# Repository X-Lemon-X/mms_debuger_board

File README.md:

## Board  debug for ModualCard system Rj45 connector
### Input
- 12V xt30 connector
- USB-C connector for MMS<-PC communication USB 2.0 compatible
- CAN1 and CAN2 molex microfit 2x2 connectors.
- 2x can termination switches
- Reverse polarity protection
### Output
- Rj45 connector for ModualCard system

### RJ45 Pinout
| Pin | Function | Description |
|-----|----------|---------------------------------------------|
| 1   | CAN1 L   | CAN 1 Low speed up to 1 Mb/s                |
| 2   | CAN1 H   | CAN 1 High speed up to 1 Mb/s               |
| 3   | GND      | 500mA                                       |
| 4   | CAN2 L   | CAN 2 Low speed up to 5 Mb/s                |
| 5   | CAN2 H   | CAN 2 High speed up to 5 Mb/s               |
| 6   | 12V      | 500 mA                                      |
| 7   | USB D-   | USB data plus                               |
| 8   | USB D+   | USB data minus                              |

### Images

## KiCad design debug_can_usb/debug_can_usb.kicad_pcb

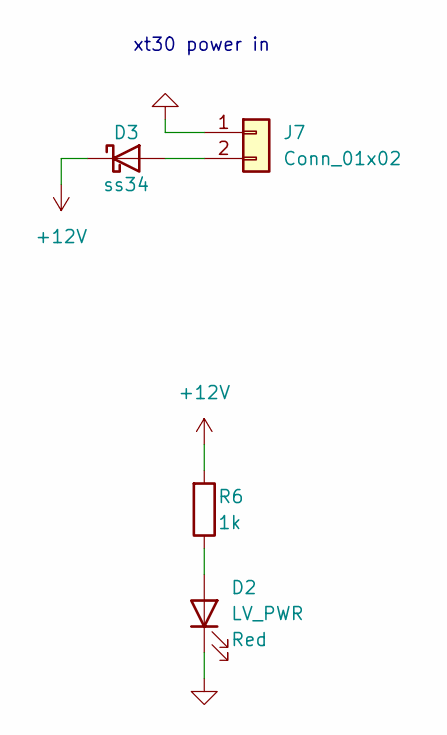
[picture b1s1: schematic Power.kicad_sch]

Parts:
D2: LV_PWR; D_0603_1608Metric
D3: ss34; D_SMA
J7: Conn_01x02; AMASS_XT30PW-M_1x02_P2.50mm_Horizontal
R6: 1k; R_0402_1005Metric

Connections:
+12V: D3.1 (K), R6.2; also elsewhere on the board
GND: D2.1 (K), J7.1; also elsewhere on the board
unnamed: D2.2 (A), R6.1
unnamed: D3.2 (A), J7.2

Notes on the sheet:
xt30 power in

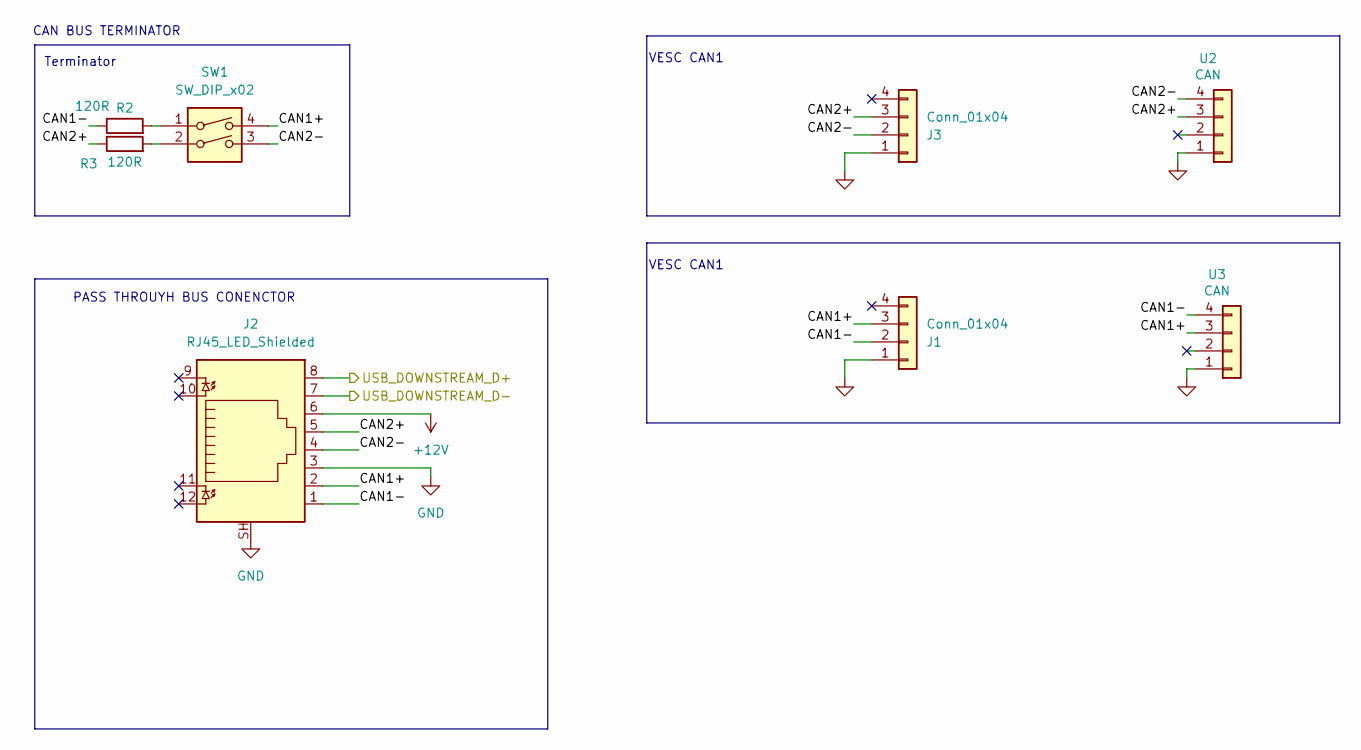
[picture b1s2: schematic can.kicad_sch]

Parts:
J1, J3: Conn_01x04; JST_XH_B4B-XH-A_1x04_P2.50mm_Vertical
J2: RJ45_LED_Shielded; RJ45_Amphenol_RJHSE538X
R2, R3: 120R; R_0603_1608Metric
SW1: SW_DIP_x02; SW_DIP_SPSTx02_Slide_6.7x6.64mm_W7.62mm_P2.54mm_LowProfile
U2, U3: CAN; Molex_Micro-Fit_3.0_43045-0412_2x02_P3.00mm_Vertical

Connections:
+12V: J2.6; also elsewhere on the board
/CAN/CAN1+: J1.3, J2.2, SW1.4, U3.3
/CAN/CAN1-: J1.2, J2.1, R2.1, U3.4
/CAN/CAN2+: J2.5, J3.3, R3.1, U2.3
/CAN/CAN2-: J2.4, J3.2, SW1.3, U2.4
/CAN/USB_DOWNSTREAM_D+: J2.8; also elsewhere on the board
/CAN/USB_DOWNSTREAM_D-: J2.7; also elsewhere on the board
GND: J1.1, J2.3, J2.SH, J3.1, U2.1, U3.1; also elsewhere on the board
unnamed: R2.2, SW1.1
unnamed: R3.2, SW1.2

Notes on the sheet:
PASS THROUYH BUS CONENCTOR
CAN BUS TERMINATOR
VESC CAN1
Terminator

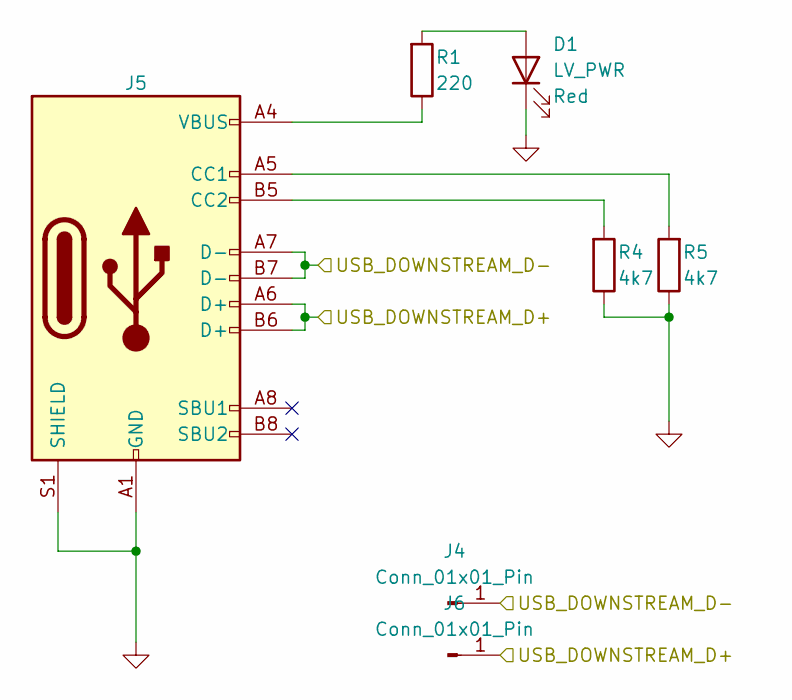
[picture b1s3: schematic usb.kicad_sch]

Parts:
D1: LV_PWR; D_0603_1608Metric
J4, J6: Conn_01x01_Pin; PinHeader_1x01_P2.54mm_Vertical
J5: USB_C_Receptacle_USB2.0; USB_C_Receptacle_G-Switch_GT-USB-7010ASV
R1: 220; R_0402_1005Metric
R4, R5: 4k7; R_0402_1005Metric

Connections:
/CAN/USB_DOWNSTREAM_D+: J5.A6 (D+), J5.B6 (D+), J6.1; also elsewhere on the board
/CAN/USB_DOWNSTREAM_D-: J4.1, J5.A7 (D-), J5.B7 (D-); also elsewhere on the board
GND: D1.1 (K), J5.A1 (GND), J5.A12 (GND), J5.B1 (GND), J5.B12 (GND), J5.S1 (SHIELD), R4.1, R5.1; also elsewhere on the board
unnamed: D1.2 (A), R1.2
unnamed: J5.A5 (CC1), R5.2
unnamed: J5.B5 (CC2), R4.2
unnamed: J5.A4 (VBUS), J5.A9 (VBUS), J5.B4 (VBUS), J5.B9 (VBUS), R1.1

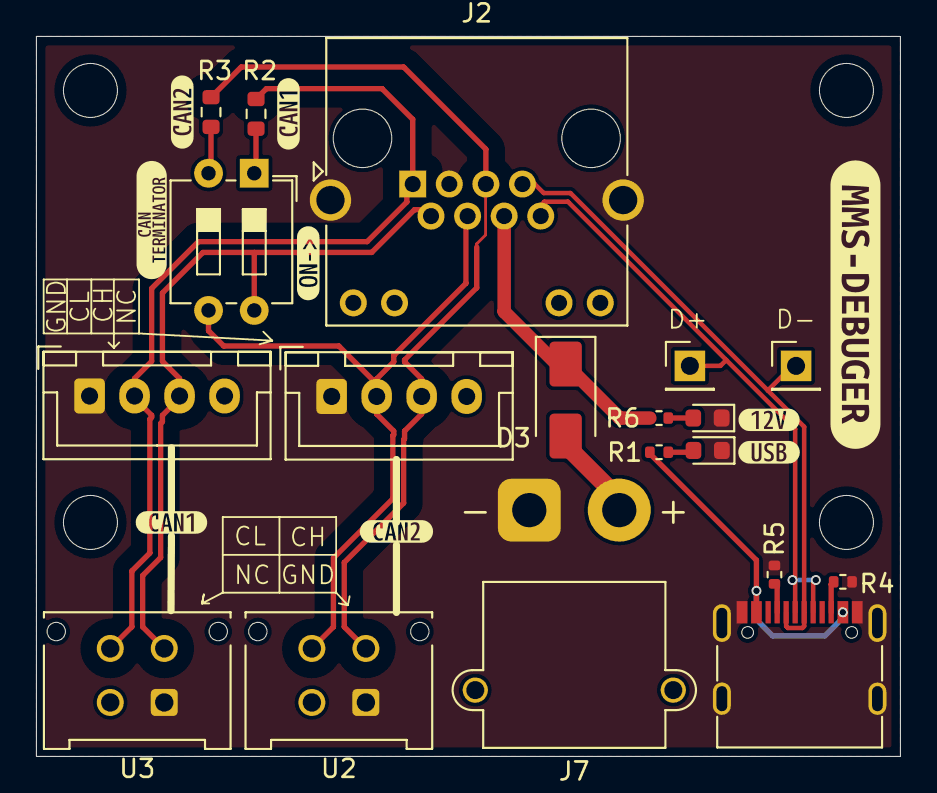
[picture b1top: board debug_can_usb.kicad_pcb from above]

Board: 2 copper layers, 48.0 x 40.0 mm, 28 parts (0 on the bottom side), 16 nets.

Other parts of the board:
kibuzzard-675D9C7D, kibuzzard-675D9C7D#2: G***; kibuzzard-675D9C7D
kibuzzard-675D9C73, kibuzzard-675D9C73#2: G***; kibuzzard-675D9C73
kibuzzard-675D9CCD: G***; kibuzzard-675D9CCD
kibuzzard-67840A5C: G***; kibuzzard-67840A5C
kibuzzard-67840A66: G***; kibuzzard-67840A66
kibuzzard-67840BAA: G***; kibuzzard-67840BAA
kibuzzard-6784102F: G***; kibuzzard-6784102F

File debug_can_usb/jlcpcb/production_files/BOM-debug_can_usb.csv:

Comment,Designator,Footprint,LCSC,Quantity
SW_DIP_x02,SW1,SW_DIP_SPSTx02_Slide_6.7x6.64mm_W7.62mm_P2.54mm_LowProfile,,1
120R,R2,R_0603_1608Metric,,1
120R,R3,R_0603_1608Metric,,1
Conn_01x01_Pin,J4,PinHeader_1x01_P2.54mm_Vertical,,1
USB_C_Receptacle_USB2.0,J5,USB_C_Receptacle_G-Switch_GT-USB-7010ASV,,1
1k,R6,R_0402_1005Metric,,1
Conn_01x01_Pin,J6,PinHeader_1x01_P2.54mm_Vertical,,1
4k7,R5,R_0402_1005Metric,,1
Conn_01x04,J1,JST_XH_B4B-XH-A_1x04_P2.50mm_Vertical,,1
RJ45_LED_Shielded,J2,RJ45_Amphenol_RJHSE538X,,1
Conn_01x04,J3,JST_XH_B4B-XH-A_1x04_P2.50mm_Vertical,,1
ss34,D3,D_SMA,,1
220,R1,R_0402_1005Metric,,1
LV_PWR,D2,D_0603_1608Metric,,1
LV_PWR,D1,D_0603_1608Metric,,1
CAN,U3,Molex_Micro-Fit_3.0_43045-0412_2x02_P3.00mm_Vertical,,1
CAN,U2,Molex_Micro-Fit_3.0_43045-0412_2x02_P3.00mm_Vertical,,1
4k7,R4,R_0402_1005Metric,,1
Conn_01x02,J7,AMASS_XT30PW-M_1x02_P2.50mm_Horizontal,,1

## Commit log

2025-01-25 rev 1.0
